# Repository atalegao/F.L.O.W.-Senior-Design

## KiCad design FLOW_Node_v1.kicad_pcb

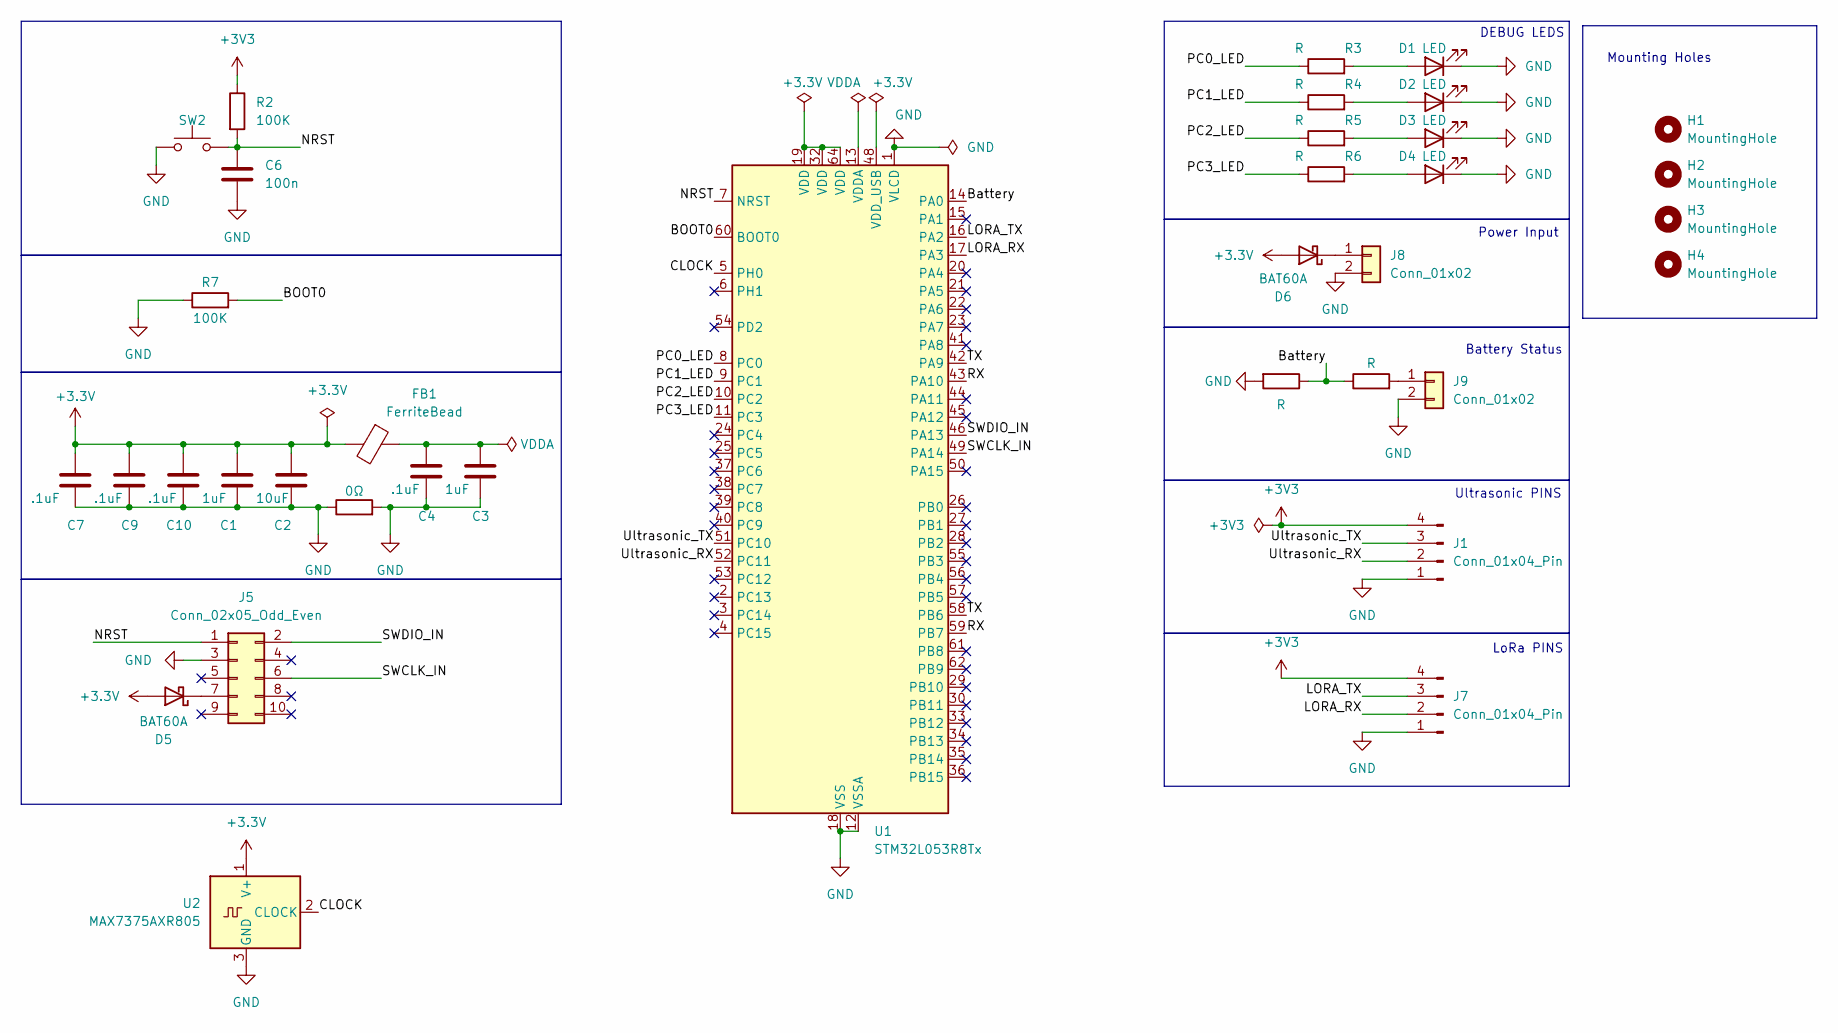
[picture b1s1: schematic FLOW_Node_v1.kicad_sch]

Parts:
C1, C3: 1uF; C_0805_2012Metric
C2: 10uF; C_0805_2012Metric
C4, C7, C9, C10: .1uF; C_0805_2012Metric
C6: 100n; C_0805_2012Metric
D1, D2, D3, D4: LED; LED_0805_2012Metric
D5, D6: BAT60A; D_SOD-323
FB1: FerriteBead; L_0805_2012Metric
H1, H2, H3, H4: MountingHole; MountingHole_3.2mm_M3
J1, J7: Conn_01x04_Pin; JST_PH_B4B-PH-K_1x04_P2.00mm_Vertical
J5: Conn_02x05_Odd_Even; PinHeader_2x05_P2.54mm_Vertical
J8, J9: Conn_01x02; JST_PH_B2B-PH-K_1x02_P2.00mm_Vertical
R1, R3, R4, R5, R6, R8: R; R_0805_2012Metric
R2, R7: 100K; R_0805_2012Metric
R9: 0Ω; R_0805_2012Metric
SW2: SW_Push_1P1T_NO_CK_KSC6xxJ
U1: STM32L053R8Tx; LQFP-64_10x10mm_P0.5mm
U2: MAX7375AXR805; SOT-323_SC-70

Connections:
+3.3V: C1.1, C2.1, C7.1, C9.1, C10.1, D5.2 (A), D6.2 (A), FB1.2, U2.1 (V+)
+3V3: J1.4, J7.4, R2.1
/BOOT0: R7.2, U1.60 (BOOT0)
/Battery: R1.1, R8.1, U1.14 (PA0)
/CLOCK: U1.5 (PH0), U2.2 (CLOCK)
/LORA_RX: J7.2, U1.17 (PA3)
/LORA_TX: J7.3, U1.16 (PA2)
/NRST: C6.1, J5.1, R2.2, SW2.2, U1.7 (NRST)
/PC0_LED: R3.1, U1.8 (PC0)
/PC1_LED: R4.1, U1.9 (PC1)
/PC2_LED: R5.1, U1.10 (PC2)
/PC3_LED: R6.1, U1.11 (PC3)
/RX: U1.43 (PA10), U1.59 (PB7)
/SWCLK_IN: J5.6, U1.49 (PA14)
/SWDIO_IN: J5.2, U1.46 (PA13)
/TX: U1.42 (PA9), U1.58 (PB6)
/Ultrasonic_RX: J1.2, U1.52 (PC11)
/Ultrasonic_TX: J1.3, U1.51 (PC10)
GND: C1.2, C2.2, C3.2, C4.2, C6.2, C7.2, C9.2, C10.2, D1.1 (K), D2.1 (K), D3.1 (K), D4.1 (K), J1.1, J5.3, J7.1, J8.2, J9.2, R1.2, R7.1, R9.1, R9.2, SW2.1, U1.1 (VLCD), U1.12 (VSSA), U1.18 (VSS), U1.31 (VSS), U1.47 (VSS), U1.63 (VSS), U2.3 (GND)
unnamed: C3.1, C4.1, FB1.1
unnamed: D1.2 (A), R3.2
unnamed: D2.2 (A), R4.2
unnamed: D3.2 (A), R5.2
unnamed: D4.2 (A), R6.2
unnamed: D5.1 (K), J5.7
unnamed: D6.1 (K), J8.1
unnamed: J9.1, R8.2
unnamed: U1.19 (VDD), U1.32 (VDD), U1.64 (VDD)

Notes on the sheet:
LoRa PINS
Mounting Holes
Battery Status
Power Input
Ultrasonic PINS
DEBUG LEDS

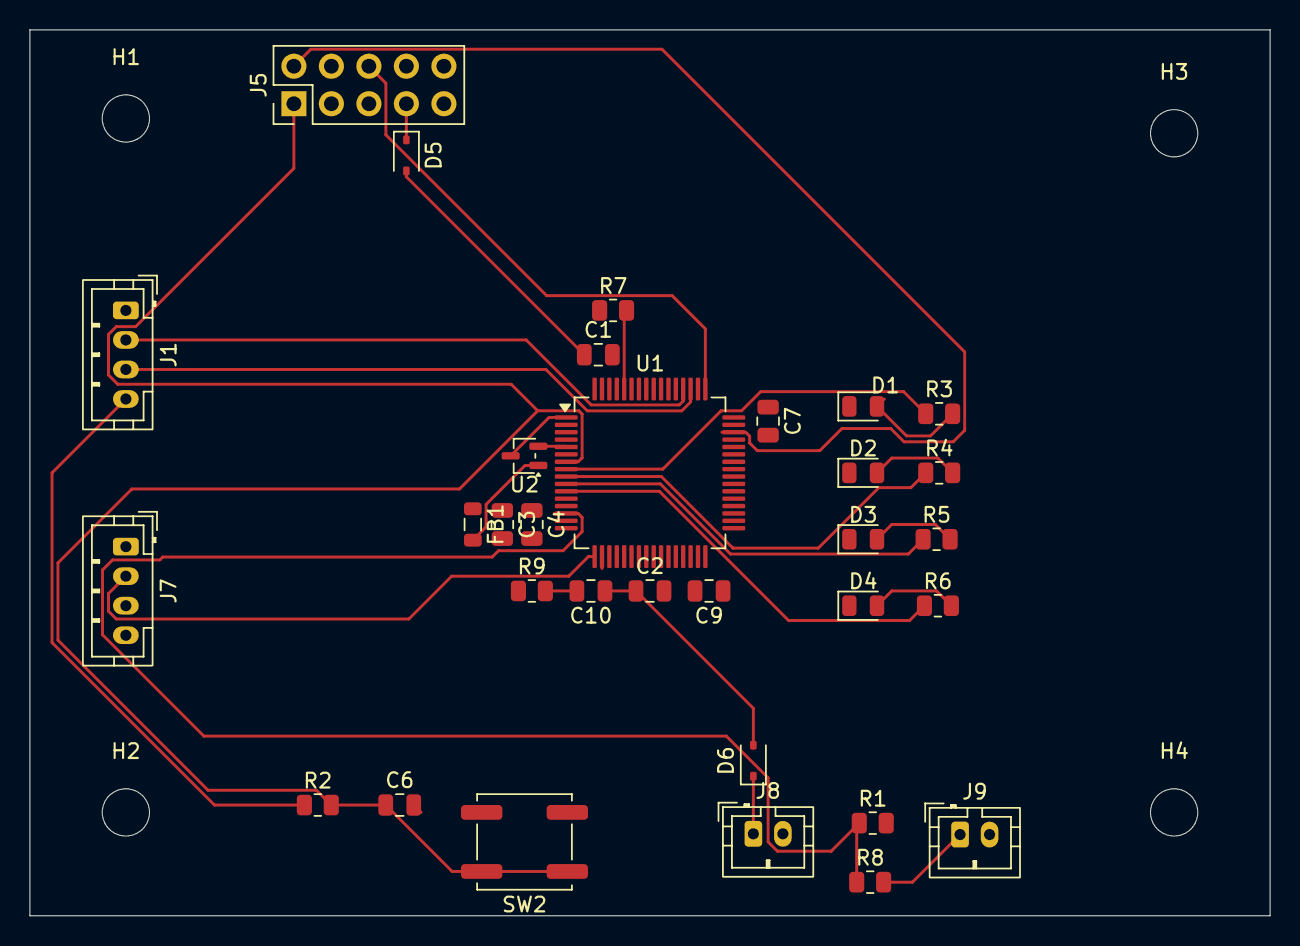
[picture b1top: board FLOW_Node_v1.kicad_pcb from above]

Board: 2 copper layers, 84.0 x 60.0 mm, 36 parts (0 on the bottom side), 28 nets.

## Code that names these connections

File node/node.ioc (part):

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Mcu.Name=STM32L053R(6-8)Tx
Mcu.Package=LQFP64
Mcu.UserName=STM32L053R8Tx
PA0.GPIOParameters=GPIO_Label
PA0.GPIO_Label=Battery
PA0.Signal=SharedAnalog_PA0
PA10.Mode=Asynchronous
PA10.Signal=USART1_RX
PA11.Signal=GPIO_Analog
PA12.Signal=GPIO_Analog
PA13.Mode=Serial_Wire
PA13.Signal=SYS_SWDIO
PA14.Mode=Serial_Wire
PA14.Signal=SYS_SWCLK
PA2.Mode=Asynchronous
PA2.Signal=USART2_TX
PA3.Mode=Asynchronous
PA3.Signal=USART2_RX
PA6.GPIOParameters=GPIO_Label
PA6.GPIO_Label=DBG_BTN1
PA6.Signal=GPIO_Input
PA7.GPIOParameters=GPIO_Label
PA7.GPIO_Label=DBG_BTN2
PA7.Signal=GPIO_Input
PA9.Mode=Asynchronous
PA9.Signal=USART1_TX
PB0.GPIOParameters=PinState,GPIO_PuPd,GPIO_Label
PB0.GPIO_Label=LORA_MOSFET
PB0.GPIO_PuPd=GPIO_NOPULL
PB0.PinState=GPIO_PIN_SET
PB0.Signal=GPIO_Output
PB10.Mode=I2C
PB10.Signal=I2C2_SCL
PB11.Mode=I2C
PB11.Signal=I2C2_SDA
PB6.GPIOParameters=GPIO_Label
PB6.GPIO_Label=TP_TX1
PB6.Signal=GPIO_Output
PB7.GPIOParameters=GPIO_Label
PB7.GPIO_Label=TP_RX1
PB7.Signal=GPIO_Output
PC10.Mode=Asynchronous
PC10.Signal=LPUART1_TX
PC11.Mode=Asynchronous
PC11.Signal=LPUART1_RX
PC2.GPIOParameters=GPIO_Label
PC2.GPIO_Label=PC0_LED
PC2.Signal=GPIO_Output
PC3.GPIOParameters=GPIO_Label
PC3.GPIO_Label=PC1_LED
PC3.Signal=GPIO_Output
PC4.GPIOParameters=GPIO_Label
PC4.GPIO_Label=PC2_LED
PC4.Signal=GPIO_Output
PC8.GPIOParameters=GPIO_Label
PC8.GPIO_Label=LORA_TGL_RELAY
PC8.Signal=GPIO_Output
PH0-OSC_IN.Signal=RCC_OSC_IN
RCC.HSE_VALUE=8000000
RCC.SYSCLKFreq_VALUE=32000000
RCC.SYSCLKSource=RCC_SYSCLKSOURCE_PLLCLK
board=custom

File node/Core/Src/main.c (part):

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				  HAL_NVIC_EnableIRQ(LPTIM1_IRQn);
				  HAL_NVIC_EnableIRQ(TIM6_DAC_IRQn);

//				  HAL_GPIO_WritePin(GPIOC, PC0_LED_Pin|PC1_LED_Pin|PC2_LED_Pin, GPIO_PIN_SET);
//				  HAL_Delay(1000);
//				  HAL_GPIO_WritePin(GPIOC, PC0_LED_Pin|PC1_LED_Pin|PC2_LED_Pin, GPIO_PIN_RESET);
			  }
			  if(do_send & (!global_receive_mode_from_cad) & (!read_lora_fifo)){
				  in_send = true;
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				  HAL_NVIC_EnableIRQ(LPTIM1_IRQn);
				  uint32_t delay = random_number_gen();//random delay
				  HAL_Delay(delay & 0x0F);
//				  HAL_GPIO_WritePin(GPIOC, PC2_LED_Pin, GPIO_PIN_SET);
//				  HAL_Delay(1000);
//				  HAL_GPIO_WritePin(GPIOC, PC2_LED_Pin, GPIO_PIN_RESET);
			  }
			  if(complete_pass > 0){
				  complete_pass = 0;
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			  HAL_NVIC_EnableIRQ(TIM21_IRQn);
			  HAL_NVIC_EnableIRQ(TIM6_DAC_IRQn);

			  HAL_GPIO_WritePin(GPIOC, PC0_LED_Pin|PC1_LED_Pin|PC2_LED_Pin, GPIO_PIN_SET);
			  HAL_Delay(1000);
			  HAL_GPIO_WritePin(GPIOC, PC0_LED_Pin|PC1_LED_Pin|PC2_LED_Pin, GPIO_PIN_RESET);
		  }
		  send_item_off_send_buffer();
	  }
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		  */
		  in_send = false;
		  HAL_Delay(100);
		  HAL_GPIO_WritePin(GPIOC, PC0_LED_Pin|PC1_LED_Pin|PC2_LED_Pin, GPIO_PIN_SET);
		  HAL_Delay(1000);
		  HAL_GPIO_WritePin(GPIOC, PC0_LED_Pin|PC1_LED_Pin|PC2_LED_Pin, GPIO_PIN_RESET);
		  //
//		  while(1){
//			  send_item_off_send_buffer();
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//		  lora_read_fifo_all(rec_data, 0x2, hdma_usart2_tx, huart2); //second input is length
//		  read_lora_fifo = false;
//		  //
//		  HAL_GPIO_WritePin(GPIOC, PC0_LED_Pin|PC1_LED_Pin|PC2_LED_Pin, GPIO_PIN_SET);
//		  HAL_Delay(1000);
//		  HAL_GPIO_WritePin(GPIOC, PC0_LED_Pin|PC1_LED_Pin|PC2_LED_Pin, GPIO_PIN_RESET);
//	  }
//	  //send message
//	  if(do_send & (!global_receive_mode_from_cad) & (!read_lora_fifo)){
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//		 data[1] = 0x0F;
//		 lora_send(data, 2, hdma_usart2_tx, huart2);
//		 do_send = false;//end send
//		 HAL_GPIO_WritePin(GPIOC, PC2_LED_Pin, GPIO_PIN_SET);
//		 HAL_Delay(1000);
//		 HAL_GPIO_WritePin(GPIOC, PC2_LED_Pin, GPIO_PIN_RESET);
//		 uint32_t delay = random_number_gen();//random delay
//		 HAL_Delay(delay & 0xFF);
//	  }
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  __HAL_RCC_GPIOD_CLK_ENABLE();

  /*Configure GPIO pin Output Level */
  HAL_GPIO_WritePin(GPIOC, PC0_LED_Pin|PC1_LED_Pin|PC2_LED_Pin|LORA_TGL_RELAY_Pin, GPIO_PIN_RESET);

  /*Configure GPIO pin Output Level */
  HAL_GPIO_WritePin(LORA_MOSFET_GPIO_Port, LORA_MOSFET_Pin, GPIO_PIN_SET);
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  /*Configure GPIO pin Output Level */
  HAL_GPIO_WritePin(GPIOB, TP_TX1_Pin|TP_RX1_Pin, GPIO_PIN_RESET);

  /*Configure GPIO pins : PC13 PC14 PC15 PC0
                           PC1 PC5 PC6 PC7
                           PC9 PC12 */
  GPIO_InitStruct.Pin = GPIO_PIN_13|GPIO_PIN_14|GPIO_PIN_15|GPIO_PIN_0
                          |GPIO_PIN_1|GPIO_PIN_5|GPIO_PIN_6|GPIO_PIN_7
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  GPIO_InitStruct.Pull = GPIO_NOPULL;
  HAL_GPIO_Init(GPIOH, &GPIO_InitStruct);

  /*Configure GPIO pins : PC0_LED_Pin PC1_LED_Pin PC2_LED_Pin LORA_TGL_RELAY_Pin */
  GPIO_InitStruct.Pin = PC0_LED_Pin|PC1_LED_Pin|PC2_LED_Pin|LORA_TGL_RELAY_Pin;
  GPIO_InitStruct.Mode = GPIO_MODE_OUTPUT_PP;
  GPIO_InitStruct.Pull = GPIO_NOPULL;
  GPIO_InitStruct.Speed = GPIO_SPEED_FREQ_LOW;
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

void connected_test_all(void){
	HAL_GPIO_WritePin(GPIOC, PC0_LED_Pin|PC1_LED_Pin|PC2_LED_Pin, GPIO_PIN_SET);//turn on all LEDs

	connected_test(&hdma_usart2_tx, &huart2);//check LoRa

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	//wait some time
	HAL_Delay(1000);

	HAL_GPIO_WritePin(GPIOC, PC0_LED_Pin|PC1_LED_Pin|PC2_LED_Pin, GPIO_PIN_RESET);//turn off all LEDs

}

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
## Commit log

2025-10-28 LoRa added
2025-11-10 header files for stm32 and LoRa module
2025-11-10 lora uart setup done and lora_init mostly done
2025-11-11 lora progress, made functions to read and write to lora registers (not send and receive messages)
2025-11-12 DMA code added for LoRa
2025-11-13 DMA setup and modules fixed, lora modules almost ready to test
2025-11-17 new lora working on hterm
2025-11-17 bits for sending and receiving a message through hterm added
2025-11-17 removed DMA and added FIFO read functions
2025-11-18 new lora send, receive does not work on hterm
2025-11-20 lora possible fixes added
2025-11-21 LoRa fixes started
2025-11-22 fixing LoRa, tried stuff
2025-11-22 LORA SENDING AND RECEIVING OF MESSAGES WORKS
2025-11-24 made functions to test lora receiving on the STM32 and fixed typos
2025-11-24 setup lora_send code
2025-11-24 functions for lora send node and lora receive node done
2025-11-25 lora receive alternating started
2025-11-25 sending and receiving alternating made
2025-11-25 added option to send one write with very long preamble for alternating
2025-11-30 lora sending on micro works sometimes?
2025-12-02 trying to fix lora using implicit header mode
2025-12-02 implict mode made
2025-12-02 lora send works
2025-12-02 lora works on terminal, sending does not on stm32
2025-12-02 receive node detects messages, but interrupt reg has extra values
2025-12-04 LoRa receive works, but FIFO pointer does not get correct addr
2025-12-08 DMA works for receive, working on sending
2025-12-10 lora_receive node changed to work with no DMA, working on DMA
2025-12-10 DMA reads somewhat work, but value is always that of the last read (not current one)
2025-12-30 DMA implemented for LoRa, receive works, send still does not work
2025-12-31 registers have same values in terminal and in stm32 right before sending tx request
2026-01-15 LoRa sending and receiving now working, was power issue
2026-01-16 added new lora init to test CAD (with longer premable length of 30 minutes)
2026-01-16 CAD mode working on terminal
2026-01-20 CAD mode testing progress, still does not work with continuous receive mode
2026-01-22 receive mode now has correct DMA and UART comments (some were wrong before)
2026-01-22 display driver added
2026-01-22 display driver code is now set up to work with the display (I think)
2026-01-22 started converting display driver code to stm32 code from arduino specifc code
2026-01-23 closer to display driver code having no Arduino code
2026-01-23 closer?
2026-01-26 Incomplete node schematic
2026-01-29 Initial commit with wifi code
2026-01-30 changed name to wifi
2026-01-30 Added LoRa code project
2026-01-30 lora now has no errors, still need to optimize using HAL functions
2026-01-30 LoRa module code cleaned up and ready to test
2026-02-02 LoRa progress interfacing with new micro, still issues
2026-02-02 LoRa UART Tx works, Rx does not
2026-02-02 UART tx and rx works for the LoRa module
2026-02-03 LoRa receiving works on new micro
2026-02-03 LoRa sending works on the new microcontroller
2026-02-03 WiFI progress
2026-02-05 screen initial commit
2026-02-05 wifi connection working
2026-02-05 Added entryPointCPP
2026-02-05 Add files via upload
    Still needs external clock, programming header and caps
2026-02-05 Add programming header, caps, and external clock
2026-02-05 display code now has fewer errors?
2026-02-05 changes, did nothing
2026-02-05 chaged file locations for display
2026-02-05 close
2026-02-05 new errors
2026-02-05 linker issues
2026-02-05 still linker issues
2026-02-06 Screen code now has no errors
2026-02-06 updated GFX in RA8875 class to have correct dimensions
2026-02-11 baud rate of SPI for display was way off of what the example had
2026-02-13 Node Schematic and PCB
2026-02-15 Updated Node PCB
2026-02-15 Newest Node PCB
    with ground plane
2026-02-16 w/barrel jack for power
2026-02-19 trying to fix screen
2026-02-20 touchscreen technically works, calibration is a bit off
2026-02-20 Touchscreen works a lot better
2026-02-23 added function to calibrate touchscreen from a past calibration, worked
2026-02-23 inital interrupt code for touchscreen control
2026-02-23 touchscreen interrupt now works
2026-02-24 lora dma is now useful
2026-02-24 display now has correct pins
2026-02-25 lora initial CAD code
2026-02-26 lora cad code progress
2026-02-26 lora cad progress, still bugs
2026-03-02 Erroneous IOC change fixed
2026-03-02 IOC change fixed
2026-03-02 IOC changes fixed
2026-03-02 3/2 Updated Node Board + BOM
    Ignore hub files and whatnot. should just look at FLOW_Node_v1 items
2026-03-03 3/3 Node changes credit to Drew
2026-03-03 Power board as of 3.3.26
2026-03-04 Hub board 3.4.26
2026-03-04 With better cap
2026-03-04 New & improved (hopefully) 3.4.26 round 2
2026-03-04 v3 3.4.26
2026-03-04 Node updates- vivian's version - don't have to sue
2026-03-04 updated node-Vivian's version-don't have to use
2026-03-06 updated Hub from TA feedback
2026-03-06 Node after TA feedback / updated DRC rules
2026-03-06 3.6.26
2026-03-06 Hub updated with LTE footprint change
2026-03-09 CAD cycle now mostly works, have not tested send or actual receive
2026-03-10 made new ioc and it broke everything
2026-03-11 CAD cycle mostly working
2026-03-11 CAD progress for internal tx contention
2026-03-11 3 different send buffers for LoRa fully added, not tested
2026-03-12 don't know
2026-03-12 3.12.26 correct ag105
2026-03-12 module broken or code is somehow very broken, CAD detection not working
2026-03-13 init problem fixed
2026-03-22 init node
2026-03-22 node setup complete plus rtc
2026-03-24 initial hub setup
2026-03-24 CAD cycle works (without sending)
2026-03-24 CAD with sending has issues
2026-03-26 CAD with sending may work
2026-03-27 lora CAD cycle with sending works (2.0)
2026-03-31 CAD works (3.0?)
2026-03-31 initial mesh stuff
2026-03-31 nothing
2026-04-01 mesh progress
2026-04-01 more mesh progress
2026-04-01 mesh progress 2.0
2026-04-02 mesh progress 3.0
2026-04-02 mesh code needs to be redone since we actually need sending addr
2026-04-02 LTE Module (Jenna attempt)
2026-04-02 more
2026-04-02 Ultrasonic code!
2026-04-03 lora for pcb
2026-04-03 mesh prog
2026-04-03 node upated with test code
2026-04-03 code uploads and LEDs turn on
2026-04-03 screen updated
2026-04-04 test code for usb-ttl added
2026-04-06 lora works on node
2026-04-06 moving into node branch, need to save first
2026-04-06 node integration. ultrasonic code updated
2026-04-07 usb-ttl works
2026-04-07 main.c updated
2026-04-07 Adding screen_test2
2026-04-07 node works on pcb and breadboard
2026-04-07 node works on breadboard and PCB
2026-04-08 mesh message_id stuff done
2026-04-09 addr direction functions and sent_message struct handling
2026-04-10 mesh errors, 83 :(
2026-04-11 mesh has no errors, will 100000% not work
2026-04-11 added function that a timer calls to resend messages that had failed...
2026-04-11 renamed mesh functions since the updated ones are in node now
2026-04-12 Hub kicad files for the 2nd version ordered
2026-04-13 2 nodes communicate, most (50%) of messages are missed
2026-04-13 easy fix, now works >75% of the time
2026-04-14 changes?
2026-04-14 Bring screen_test2 from main into hub
2026-04-14 added send buffer and sent message buffer, improved debug prints
2026-04-14 added code to test an individual mesh send function
2026-04-14 mesh send data fixes
2026-04-15 hub integration
2026-04-15 node data sending and receiving work
2026-04-15 ack send and rec works
2026-04-15 poll works as well
2026-04-15 dead message works
2026-04-15 message type add works
2026-04-15 all mesh message types work
2026-04-16 neighbor node stuff made
2026-04-16 wait pin changed to input (not in ioc file)
2026-04-17 commented out main.c to make it use main.cpp
2026-04-17 changing polling frequency works
2026-04-17 code to test neighbor nodes works
2026-04-19 screen updates
2026-04-20 resending and message id stuff closer, made nodes send acks sometimes
2026-04-20 basic stuff not broken??
2026-04-20 LoRa integated with hub now. continuing issues with interrupts
2026-04-20 16 byte buffer in lora module sucks
2026-04-20 changes to hal_msp to possibly fix interrupt priorities
2026-04-21 int fixes
2026-04-21 code to send own data and hello messages on timers
2026-04-21 crc for add message type
2026-04-21 all crc done, not tested
2026-04-22 volatile changes
2026-04-22 mesh works?
2026-04-22 wifi module
2026-04-22 updated ultrasonic for pcb
2026-04-22 switched to one read_fifo, and all fun stuff that went with it
2026-04-22 usb-ttl rtc time setting works, is currently blocking
2026-04-22 mesh and UI linked
2026-04-22 wifi cubeide main code
2026-04-22 Ultrasonic with rx as pointer
2026-04-22 WIFIIIII!
    i added some helpful comments + changed lora to correct uart configuration.
2026-04-22 pre optimization
2026-04-22 ultrasonic works
2026-04-22 user input done, sending self add message done
2026-04-23 some useless changes for you chaps
2026-04-23 properly stops sending on another node passing it on, sends acks for som
2026-04-23 banned addr works
2026-04-23 battery status made
2026-04-23 wifi works. ready to link w lora stuff
2026-04-23 normal functionality works, main is setup correctly
2026-04-23 updates with mesh code
2026-04-23 despair
2026-04-23 cpp mess fixes
2026-04-23 starting to work
2026-04-23 continuing to debug
2026-04-23 hello message ignore fixed
2026-04-23 made backwards go faster
2026-04-27 timing optimizations (if only I did this before the demo)
2026-04-30 final

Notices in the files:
node/Core/Src/main.c:
Copyright (c) 2026 STMicroelectronics.
All rights reserved.
This software is licensed under terms that can be found in the LICENSE file
